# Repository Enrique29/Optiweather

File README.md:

# Optiweather

Proyecto para hacer modulo de monitoreo con un esp8266 utilizando webpages con boottrap y bases de datos [IoT]

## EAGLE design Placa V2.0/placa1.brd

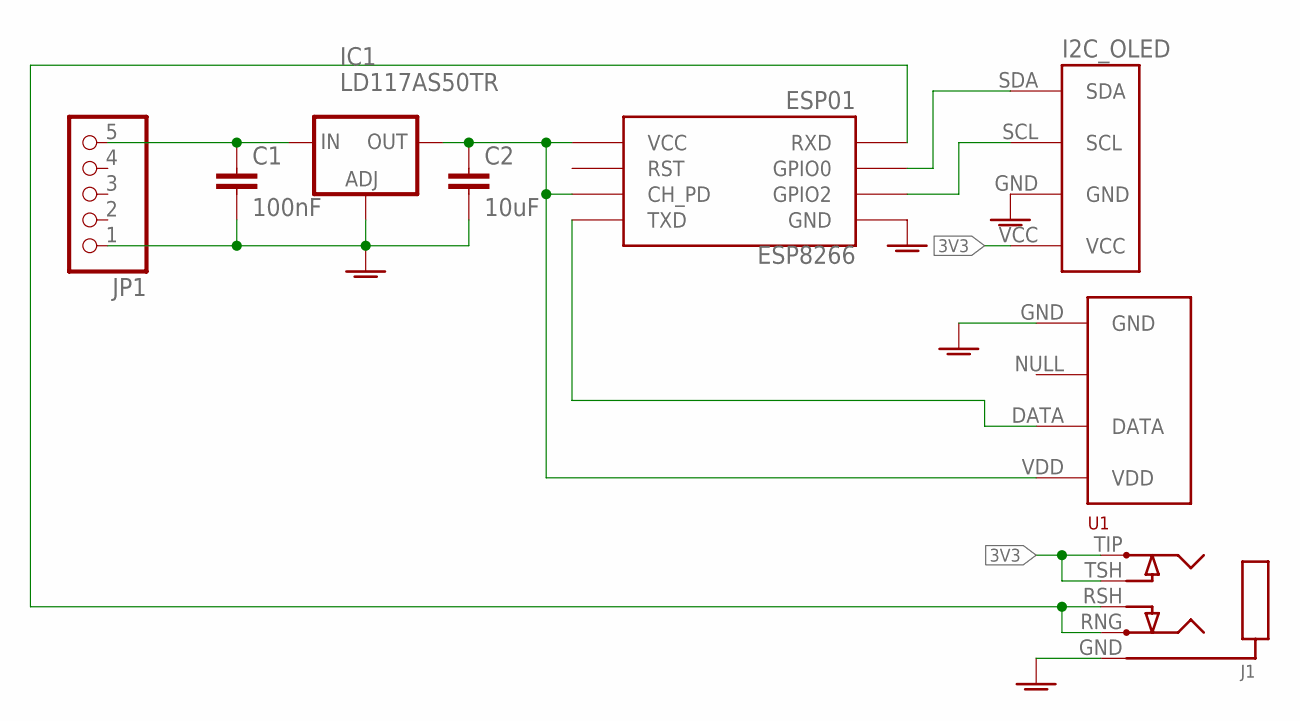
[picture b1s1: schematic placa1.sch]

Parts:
C1: 100nF; C1206K
C2: 10uF; C1206K
ESP8266: ESP01
IC1: LD117AS50TR; SOT223
J1: STEREOJACKSJ1-352XNG; SJ1-352XNG
JP1: PINHD-1X5; 1X05
OLED: I2C_OLED; I2C_OLED_PACKAGE
U1: RHT03_DHT-22_AM2302RA; RHT03_DHT-22/RA

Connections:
3V3: C2.1, ESP8266.CH_PD, ESP8266.VCC, IC1.2 (OUT), J1.TIP, J1.TSH, OLED.VCC, U1.VDD
5V: C1.1, IC1.3 (IN), JP1.5
DATA: ESP8266.TX (TXD), U1.DATA
GND: C1.2, C2.2, ESP8266.GND, IC1.1 (ADJ), J1.GND, JP1.1, OLED.GND, U1.GND
unnamed: ESP8266.GPIO2, OLED.SCL
RX: ESP8266.RX (RXD), J1.RNG, J1.RSH
SDA: ESP8266.GPIO0, OLED.SDA

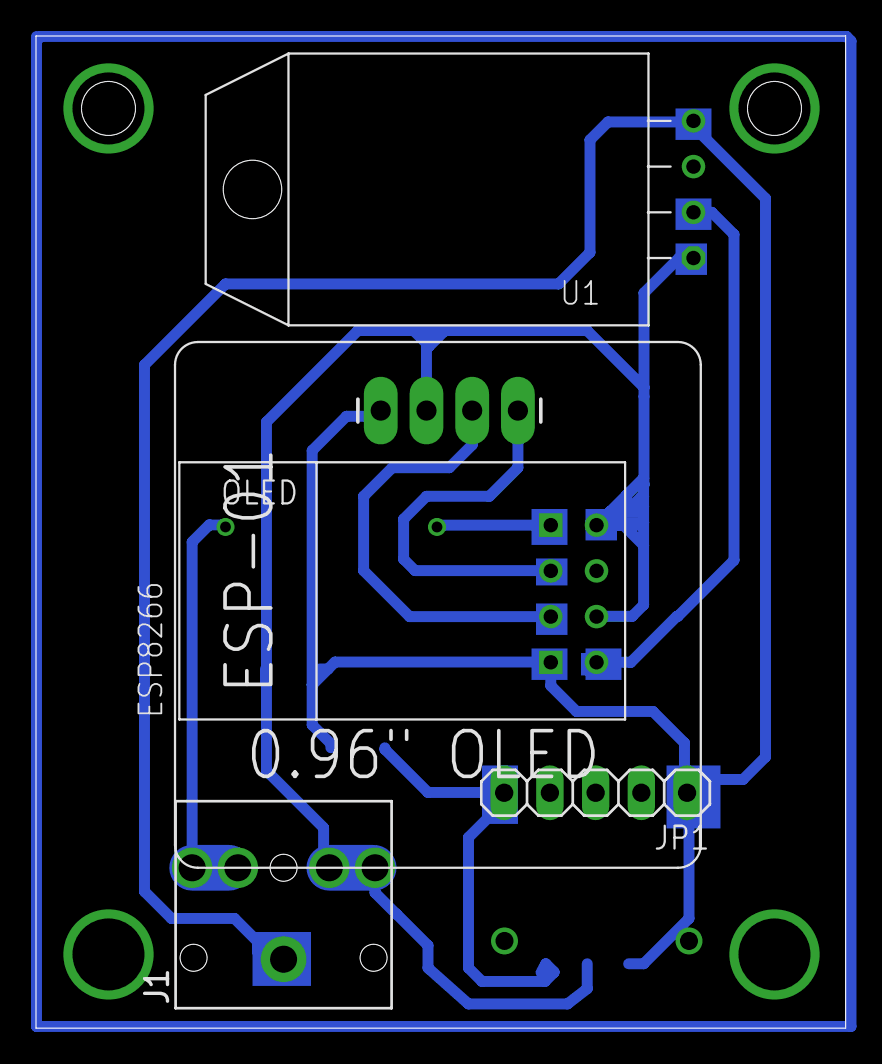
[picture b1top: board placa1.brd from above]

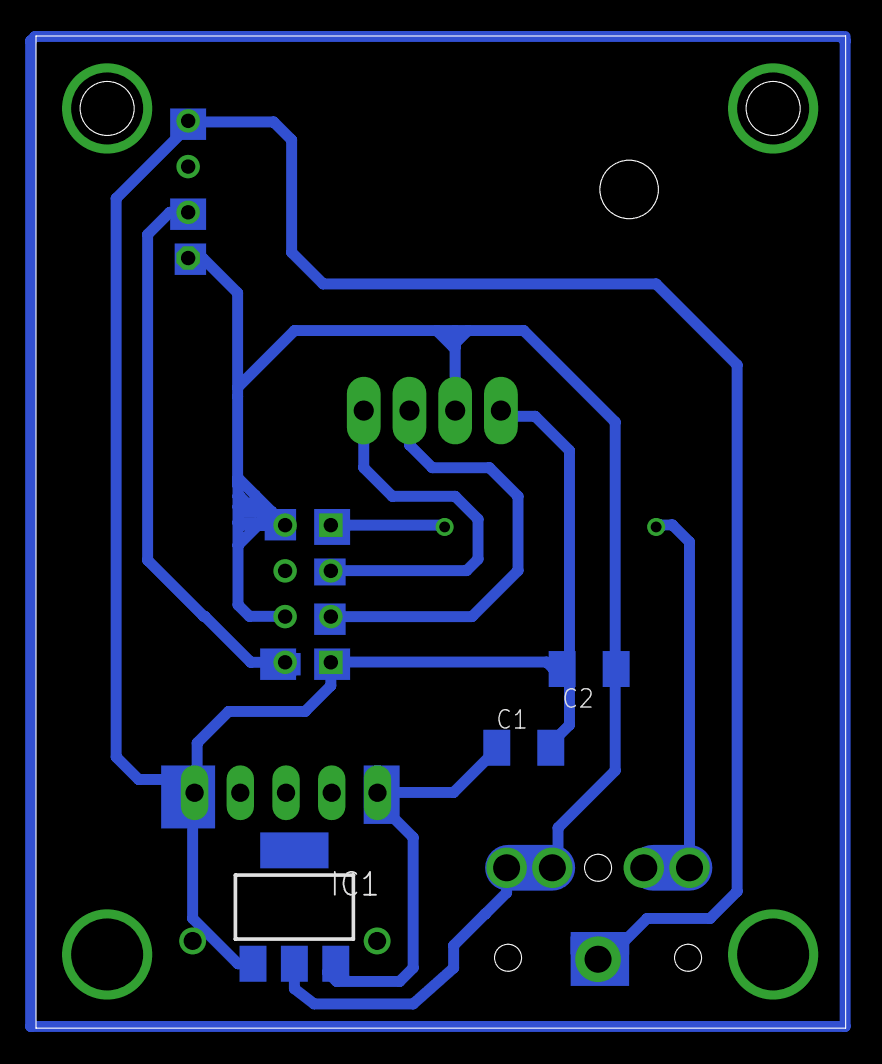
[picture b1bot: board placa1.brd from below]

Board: 2 copper layers, 45.0 x 55.1 mm, 8 parts (3 on the bottom side), 7 nets.

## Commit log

2017-06-11 Primer commit creacion del branch
2017-06-11 Agregando Links revisar y corección de error
2017-06-12 Bootstrap añadido a webpage
2017-06-14 Agregados datos de trabajo del lunes (correcciones)
2017-06-14 Modificaciones de MySQL
2017-06-15 cambios en la parte de MySQL falta corregir
2017-06-15 corregir httpclient
2017-06-16 salio el httpclient
2017-06-16 proyecto casi final falta cambiar la subida de datos
2017-06-21 cambiando a ajax
2017-06-22 cambio ahora con modo ST_AP
2017-06-26 Terminados cambios y verificaciones en ajax y cambio de ventanas Changes to be committed:
2017-06-28 Mejoras en la interfaz y ahora se saca fecha y hora del servidor
2017-06-30 ctualización
2017-07-11 Super actualización
2017-07-13 cambios en placa
2017-07-18 cambios con bug de pantalla
2018-02-26 Cambios finales del proyecto
2018-02-26 Borrando archivos no necesarios
